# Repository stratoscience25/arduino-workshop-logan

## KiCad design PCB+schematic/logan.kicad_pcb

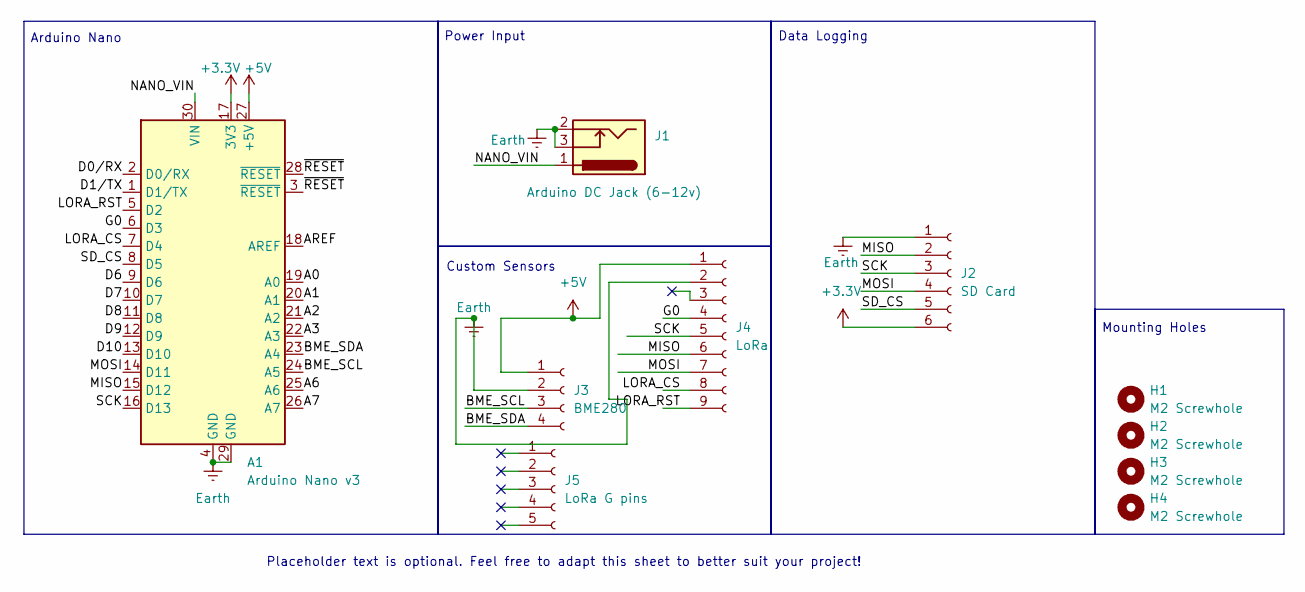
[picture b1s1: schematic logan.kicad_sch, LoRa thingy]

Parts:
A1: Arduino Nano v3; Arduino_Nano
H1, H2, H3, H4: M2 Screwhole; MountingHole_2.2mm_M2
J1: Arduino DC Jack (6-12v); BarrelJack_GCT_DCJ200-10-A_Horizontal
J2: SD Card; PinHeader_1x06_P2.54mm_Vertical
J3: BME280; PinHeader_1x04_P2.54mm_Vertical
J4: LoRa; PinHeader_1x09_P2.54mm_Vertical
J5: LoRa G pins; PinHeader_1x05_P2.54mm_Vertical

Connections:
+3.3V: A1.17 (3V3), J2.6
+5V: A1.27 (+5V), J3.1, J4.1
/A0: A1.19 (A0)
/A1: A1.20 (A1)
/A2: A1.21 (A2)
/A3: A1.22 (A3)
/A6: A1.25 (A6)
/A7: A1.26 (A7)
/AREF: A1.18 (AREF)
/BME_SCL: A1.24 (A5), J3.3
/BME_SDA: A1.23 (A4), J3.4
/D0/RX: A1.2 (D0/RX)
/D1/TX: A1.1 (D1/TX)
/D6: A1.9 (D6)
/D7: A1.10 (D7)
/D8: A1.11 (D8)
/D9: A1.12 (D9)
/D10: A1.13 (D10)
/G0: A1.6 (D3), J4.4
/LORA_CS: A1.7 (D4), J4.8
/LORA_RST: A1.5 (D2), J4.9
/MISO: A1.15 (D12), J2.2, J4.6
/MOSI: A1.14 (D11), J2.4, J4.7
/NANO_VIN: A1.30 (VIN), J1.1
/SCK: A1.16 (D13), J2.3, J4.5
/SD_CS: A1.8 (D5), J2.5
/~RESET: A1.3 (~RESET), A1.28 (~RESET)
Earth: A1.4 (GND), A1.29 (GND), J1.2, J1.3, J2.1, J3.2, J4.2

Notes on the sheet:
Data Logging
Custom Sensors
Power Input
Arduino Nano
Placeholder text is optional. Feel free to adapt this sheet to better suit your project!
Mounting Holes

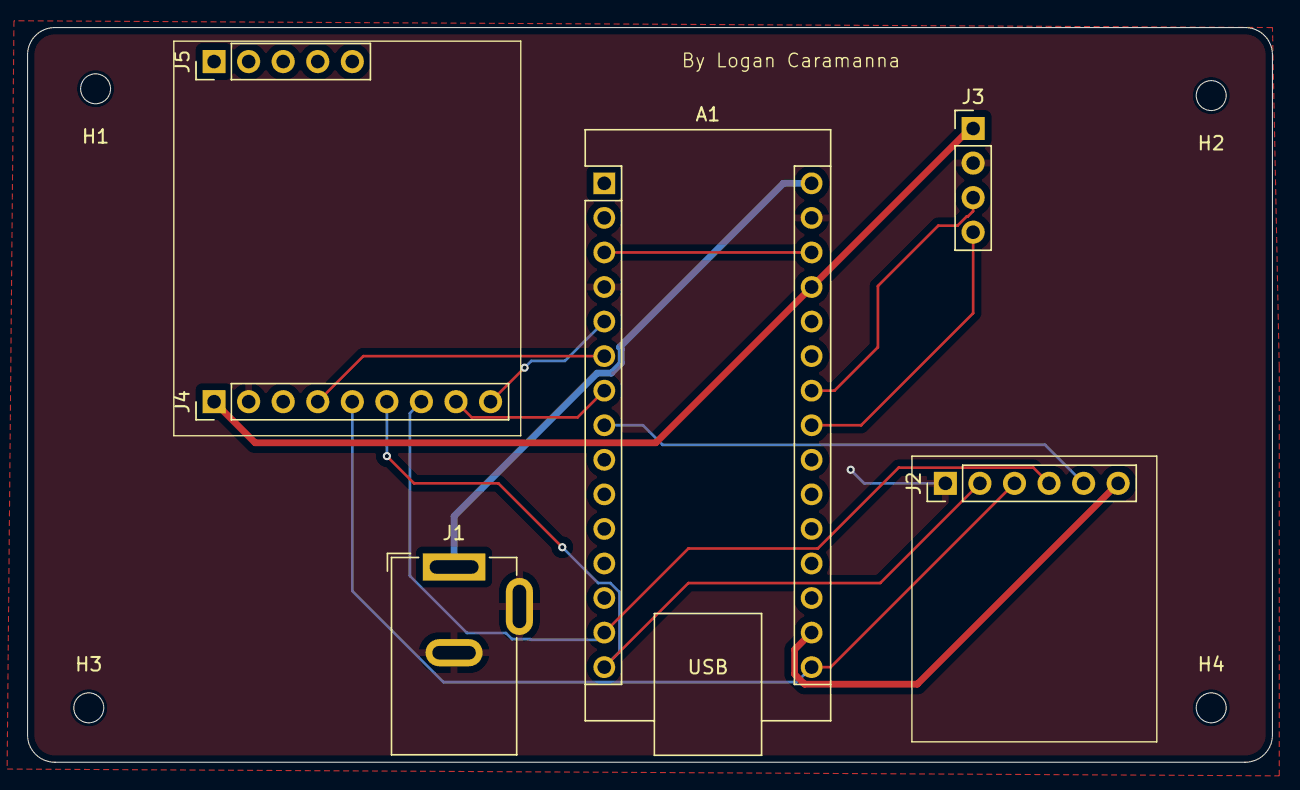
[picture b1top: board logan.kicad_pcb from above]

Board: 2 copper layers, 91.5 x 54.0 mm, 10 parts (0 on the bottom side), 14 nets.

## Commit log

2025-01-11 add files
2025-04-12 weird arduino thingy
2025-04-12 fix datastring
2025-04-12 disable using pin 13 as led pin-maybe cause of weird SD-lora SPI problem because pin 13 set as output?
2025-05-03 kicad
2025-05-03 pcb stuff
2025-05-03 Completely redo code
2025-05-10 Update .gitignore
    Fixed the lock file uploading issue
2025-05-10 Update fp-info-cache
2025-05-17 update PCB
2025-05-24 rename
2025-06-07 fix issues... maybe
2025-06-11 Create LICENSE
2025-06-15 fix spi conflict panic
2025-06-28 update files
2025-06-28 push
2025-08-07 Add presentation
2025-08-07 change gitignore
2025-08-09 change filename
2025-08-09 add pcb screenshots
2025-08-09 add more pcb screenshots and update presentation wording
2025-08-17 Rename 20250731_170617-removebg-preview.png to ground station.png
